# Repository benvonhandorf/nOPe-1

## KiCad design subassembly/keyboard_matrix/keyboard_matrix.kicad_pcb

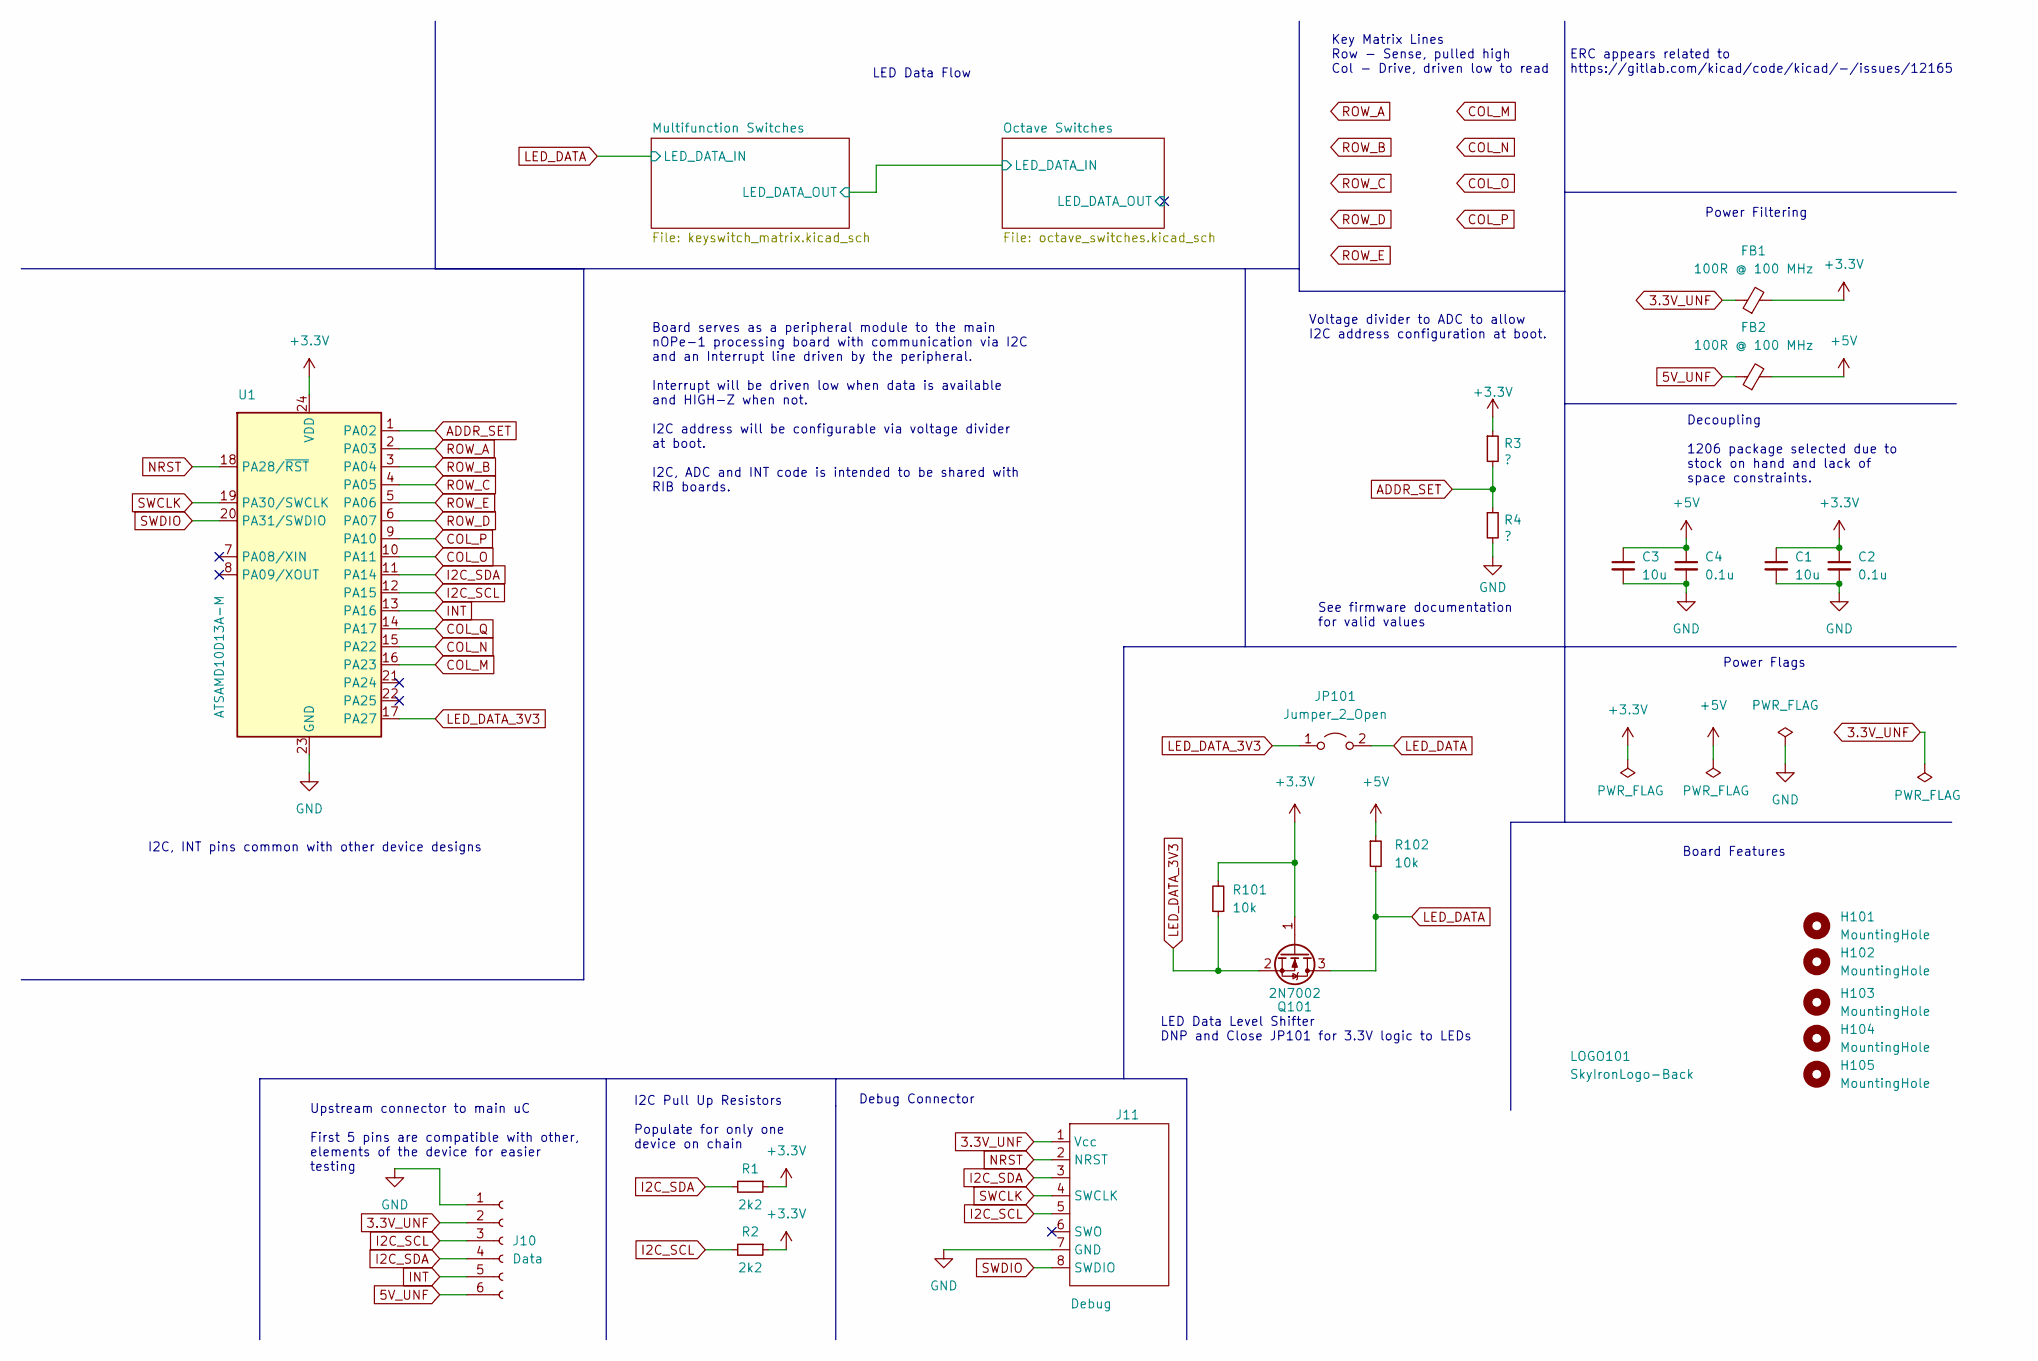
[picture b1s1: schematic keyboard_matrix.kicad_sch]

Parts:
C1, C3: 10u; C_1206_3216Metric_Pad1.33x1.80mm_HandSolder
C2, C4: 0.1u; C_1206_3216Metric_Pad1.33x1.80mm_HandSolder
FB1, FB2: 100R @ 100 MHz; R_0805_2012Metric_Pad1.20x1.40mm_HandSolder
H101, H102, H103, H104, H105: MountingHole; MountingHole_3.2mm_M3_DIN965
J10: Data; PinHeader_1x06_P2.54mm_Vertical
J11: Debug; SOICbite_renumbered
JP101: Jumper_2_Open; SolderJumper-2_P1.3mm_Open_Pad1.0x1.5mm
LOGO101: SkyIronLogo-Back; SkyIron_logo_Back
Q101: 2N7002; SOT-23
R1, R2: 2k2; R_0603_1608Metric
R3, R4: ?; R_0603_1608Metric
R101, R102: 10k; R_0805_2012Metric_Pad1.20x1.40mm_HandSolder
U1: ATSAMD10D13A-M; QFN-24-1EP_4x4mm_P0.5mm_EP2.6x2.6mm

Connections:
3.3V_UNF: FB1.1, J10.2, J11.1 (Vcc)
5V_UNF: FB2.1, J10.6
+3.3V: C1.1, C2.1, FB1.2, Q101.1 (G), R1.1, R2.1, R3.1, R101.2, U1.24 (VDD)
+5V: C3.1, C4.1, FB2.2, R102.1; also elsewhere on the board
ADDR_SET: R3.2, R4.1, U1.1 (PA02)
COL_M: U1.16 (PA23); also elsewhere on the board
COL_N: U1.15 (PA22); also elsewhere on the board
COL_O: U1.10 (PA11); also elsewhere on the board
COL_P: U1.9 (PA10); also elsewhere on the board
COL_Q: U1.14 (PA17); also elsewhere on the board
GND: C1.2, C2.2, C3.2, C4.2, J10.1, J11.7 (GND), R4.2, U1.23 (GND), U1.25 (GND); also elsewhere on the board
I2C_SCL: J10.3, J11.5, R2.2, U1.12 (PA15)
I2C_SDA: J10.4, J11.3, R1.2, U1.11 (PA14)
INT: J10.5, U1.13 (PA16)
LED_DATA: JP101.2 (B), Q101.3 (D), R102.2; also elsewhere on the board
LED_DATA_3V3: JP101.1 (A), Q101.2 (S), R101.1, U1.17 (PA27)
NRST: J11.2 (NRST), U1.18 (PA28/~RST)
ROW_A: U1.2 (PA03); also elsewhere on the board
ROW_B: U1.3 (PA04); also elsewhere on the board
ROW_C: U1.4 (PA05); also elsewhere on the board
ROW_D: U1.6 (PA07); also elsewhere on the board
ROW_E: U1.5 (PA06); also elsewhere on the board
SWCLK: J11.4 (SWCLK), U1.19 (PA30/SWCLK)
SWDIO: J11.8 (SWDIO), U1.20 (PA31/SWDIO)

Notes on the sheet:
I2C, INT pins common with other device designs
LED Data Flow
Upstream connector to main uC First 5 pins are compatible with other, elements of the device for easier testing
Power Flags
Voltage divider to ADC to allow I2C address configuration at boot.
LED Data Level Shifter DNP and Close JP101 for 3.3V logic to LEDs
I2C Pull Up Resistors Populate for only one device on chain
Board Features
Key Matrix Lines Row - Sense, pulled high Col - Drive, driven low to read
See firmware documentation for valid values
Debug Connector
Board serves as a peripheral module to the main nOPe-1 processing board with communication via I2C and an Interrupt line driven by the peripheral. Interrupt will be driven low when data is available and HIGH-Z when not. I2C address will be configurable via voltage divider at boot. I2C, ADC and INT 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
ERC appears related to https://gitlab.com/kicad/code/kicad/-/issues/12165
Decoupling 1206 package selected due to stock on hand and lack of space constraints.
Power Filtering

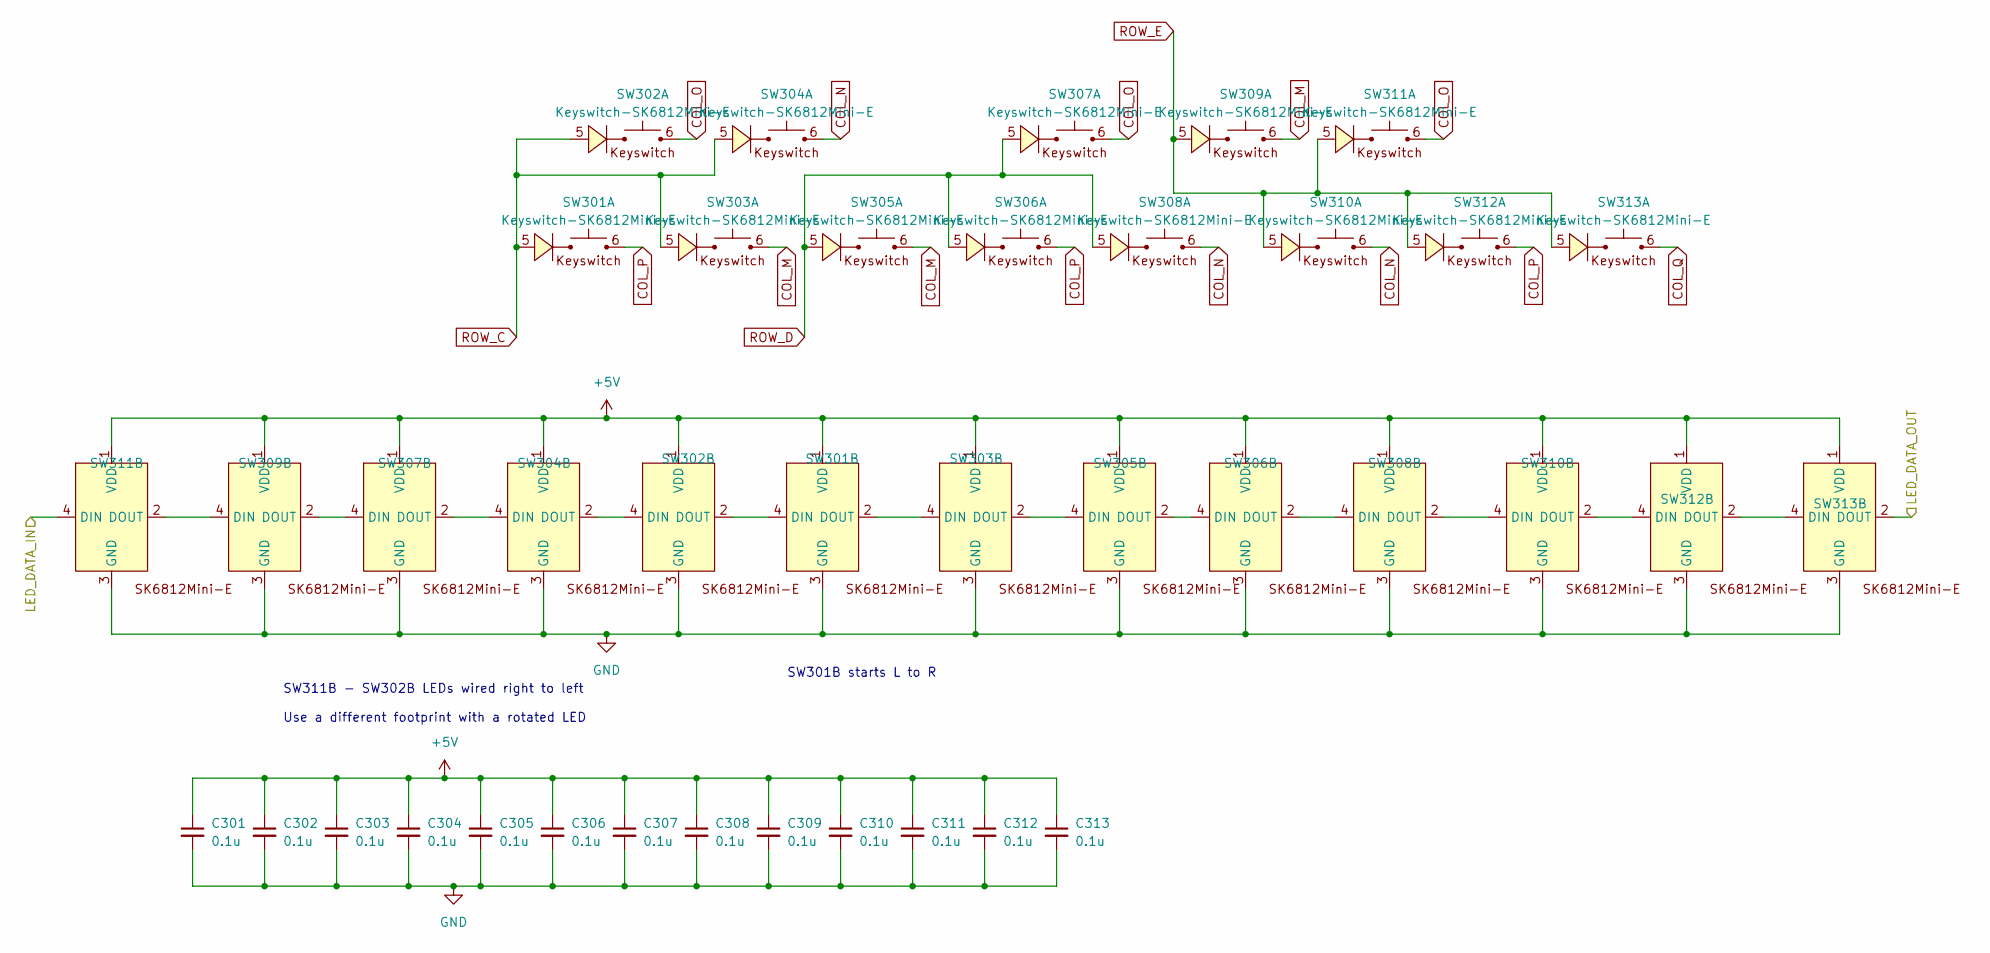
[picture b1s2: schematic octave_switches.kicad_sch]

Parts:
C301, C302, C303, C304, C305, C306, C307, C308, C309, C310, C311, C312, C313: 0.1u; C_1206_3216Metric_Pad1.33x1.80mm_HandSolder
SW301, SW303, SW305, SW306: Keyswitch-SK6812Mini-E; Keyswitch_Choc_SK6812_Diode_Vert_L
SW302, SW304, SW307, SW309, SW311: Keyswitch-SK6812Mini-E; Keyswitch_Choc_w_SK6812Mini-E_Back_SOD-103_Diode_RtoL
SW308, SW310, SW312, SW313: Keyswitch-SK6812Mini-E; Keyswitch_Choc_SK6812_Diode_Vert_R

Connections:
+5V: C301.1, C302.1, C303.1, C304.1, C305.1, C306.1, C307.1, C308.1, C309.1, C310.1, C311.1, C312.1, C313.1, SW301.1 (VDD), SW302.1 (VDD), SW303.1 (VDD), SW304.1 (VDD), SW305.1 (VDD), SW306.1 (VDD), SW307.1 (VDD), SW308.1 (VDD), SW309.1 (VDD), SW310.1 (VDD), SW311.1 (VDD), SW312.1 (VDD), SW313.1 (VDD); also elsewhere on the board
/Multifunction Switches/LED_DATA_OUT: SW311.4 (DIN); also elsewhere on the board
/Octave Switches/LED_DATA_OUT: SW313.2 (DOUT)
COL_M: SW303.6, SW305.6, SW309.6; also elsewhere on the board
COL_N: SW304.6, SW308.6, SW310.6; also elsewhere on the board
COL_O: SW302.6, SW307.6, SW311.6; also elsewhere on the board
COL_P: SW301.6, SW306.6, SW312.6; also elsewhere on the board
COL_Q: SW313.6; also elsewhere on the board
GND: C301.2, C302.2, C303.2, C304.2, C305.2, C306.2, C307.2, C308.2, C309.2, C310.2, C311.2, C312.2, C313.2, SW301.3 (GND), SW302.3 (GND), SW303.3 (GND), SW304.3 (GND), SW305.3 (GND), SW306.3 (GND), SW307.3 (GND), SW308.3 (GND), SW309.3 (GND), SW310.3 (GND), SW311.3 (GND), SW312.3 (GND), SW313.3 (GND); also elsewhere on the board
unnamed: SW301.2 (DOUT), SW303.4 (DIN)
unnamed: SW301.4 (DIN), SW302.2 (DOUT)
unnamed: SW302.4 (DIN), SW304.2 (DOUT)
unnamed: SW303.2 (DOUT), SW305.4 (DIN)
unnamed: SW304.4 (DIN), SW307.2 (DOUT)
unnamed: SW305.2 (DOUT), SW306.4 (DIN)
unnamed: SW306.2 (DOUT), SW308.4 (DIN)
unnamed: SW307.4 (DIN), SW309.2 (DOUT)
unnamed: SW308.2 (DOUT), SW310.4 (DIN)
unnamed: SW309.4 (DIN), SW311.2 (DOUT)
unnamed: SW310.2 (DOUT), SW312.4 (DIN)
unnamed: SW312.2 (DOUT), SW313.4 (DIN)
ROW_C: SW301.5, SW302.5, SW303.5, SW304.5; also elsewhere on the board
ROW_D: SW305.5, SW306.5, SW307.5, SW308.5; also elsewhere on the board
ROW_E: SW309.5, SW310.5, SW311.5, SW312.5, SW313.5; also elsewhere on the board

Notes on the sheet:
SW301B starts L to R
SW311B - SW302B LEDs wired right to left Use a different footprint with a rotated LED

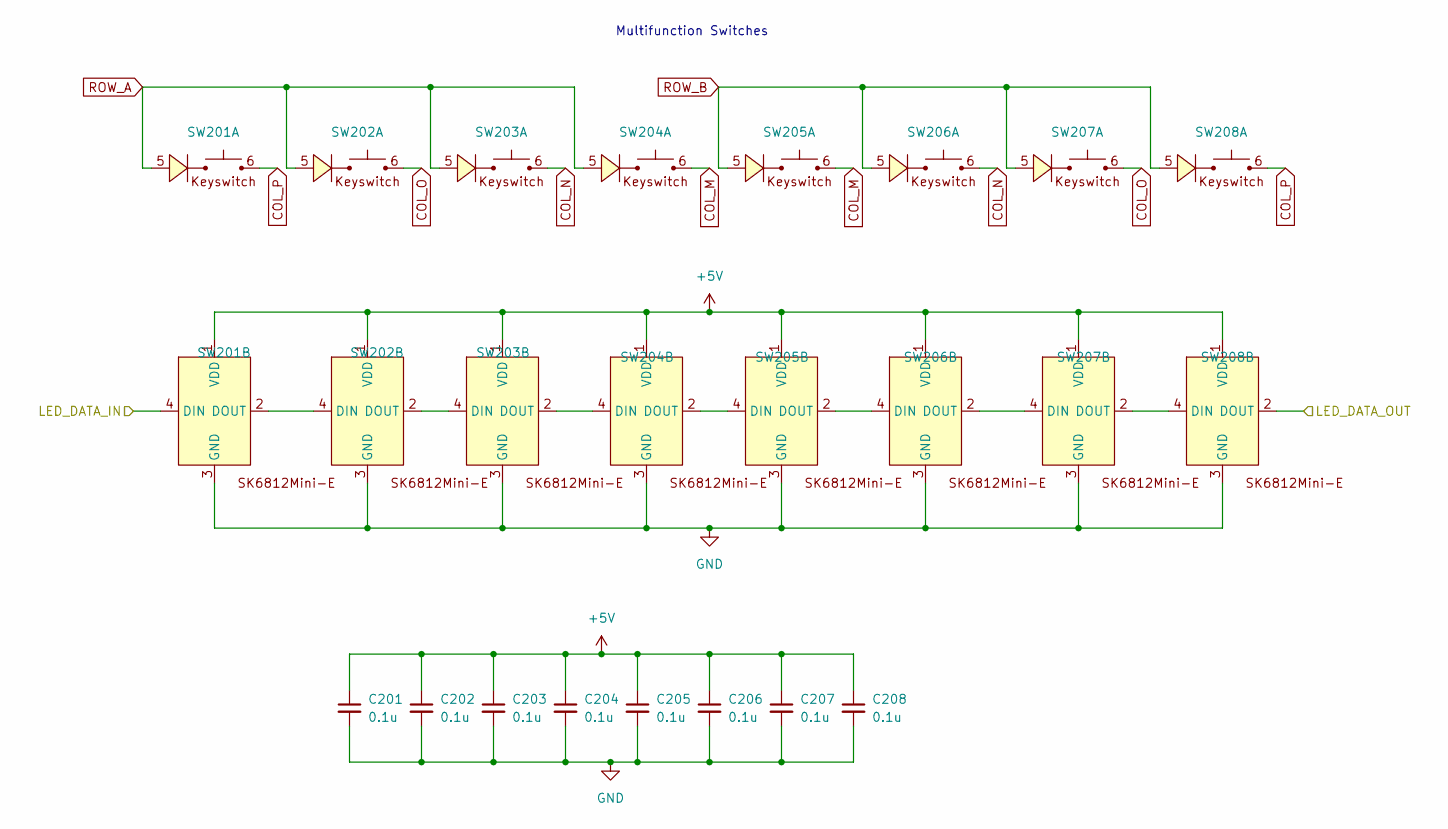
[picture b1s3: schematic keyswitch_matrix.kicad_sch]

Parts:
C201, C202, C203, C204, C205, C206, C207, C208: 0.1u; C_1206_3216Metric_Pad1.33x1.80mm_HandSolder
SW201, SW202, SW203, SW204, SW205, SW206, SW207, SW208: Keyswitch-SK6812Mini-E; Keyswitch_Choc_w_SK6812Mini-E_Back_SOD-103_Diode_LtoR

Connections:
+5V: C201.1, C202.1, C203.1, C204.1, C205.1, C206.1, C207.1, C208.1, SW201.1 (VDD), SW202.1 (VDD), SW203.1 (VDD), SW204.1 (VDD), SW205.1 (VDD), SW206.1 (VDD), SW207.1 (VDD), SW208.1 (VDD); also elsewhere on the board
/Multifunction Switches/LED_DATA_OUT: SW208.2 (DOUT); also elsewhere on the board
COL_M: SW204.6, SW205.6; also elsewhere on the board
COL_N: SW203.6, SW206.6; also elsewhere on the board
COL_O: SW202.6, SW207.6; also elsewhere on the board
COL_P: SW201.6, SW208.6; also elsewhere on the board
GND: C201.2, C202.2, C203.2, C204.2, C205.2, C206.2, C207.2, C208.2, SW201.3 (GND), SW202.3 (GND), SW203.3 (GND), SW204.3 (GND), SW205.3 (GND), SW206.3 (GND), SW207.3 (GND), SW208.3 (GND); also elsewhere on the board
LED_DATA: SW201.4 (DIN); also elsewhere on the board
unnamed: SW201.2 (DOUT), SW202.4 (DIN)
unnamed: SW202.2 (DOUT), SW203.4 (DIN)
unnamed: SW203.2 (DOUT), SW204.4 (DIN)
unnamed: SW204.2 (DOUT), SW205.4 (DIN)
unnamed: SW205.2 (DOUT), SW206.4 (DIN)
unnamed: SW206.2 (DOUT), SW207.4 (DIN)
unnamed: SW207.2 (DOUT), SW208.4 (DIN)
ROW_A: SW201.5, SW202.5, SW203.5, SW204.5; also elsewhere on the board
ROW_B: SW205.5, SW206.5, SW207.5, SW208.5; also elsewhere on the board

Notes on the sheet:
Multifunction Switches

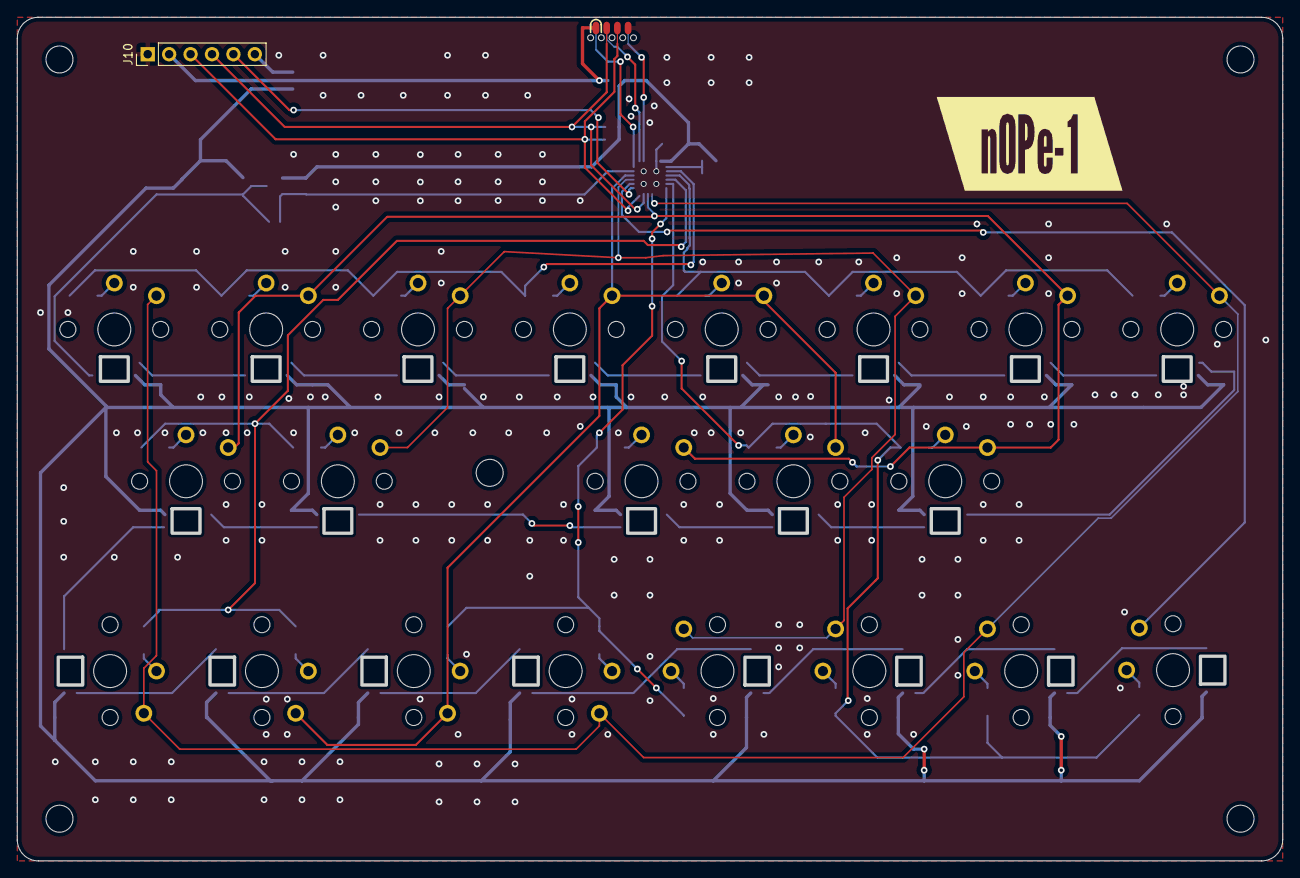
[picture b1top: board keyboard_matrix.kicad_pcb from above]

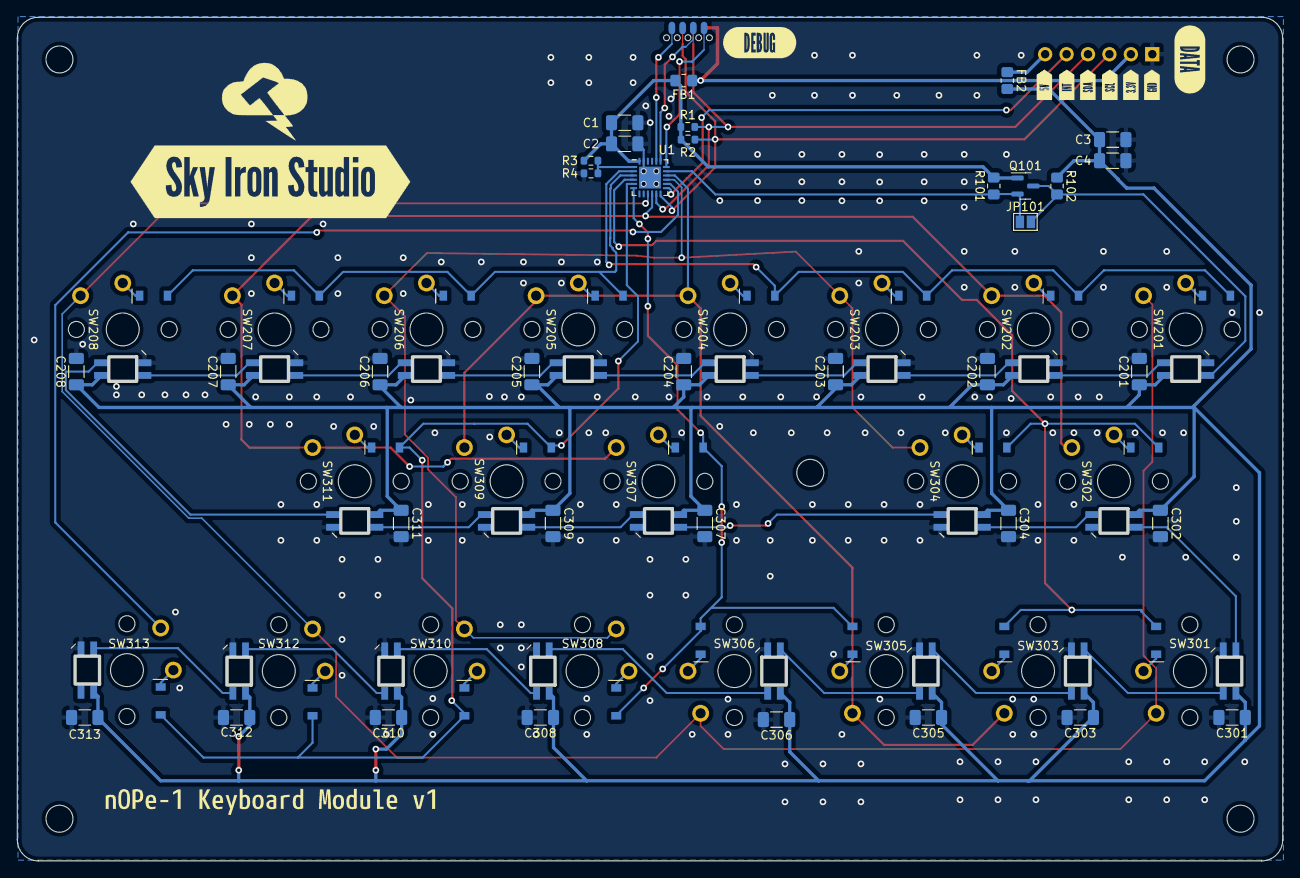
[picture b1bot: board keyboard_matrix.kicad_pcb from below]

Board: 2 copper layers, 149.7 x 99.7 mm, 76 parts (46 on the bottom side), 44 nets.

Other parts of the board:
kibuzzard-6388C4FD: G***; kibuzzard-6388C4FD
kibuzzard-6388C06F: G***; kibuzzard-6388C06F
kibuzzard-6388C51A: G***; kibuzzard-6388C51A
kibuzzard-6388C61B: G***; kibuzzard-6388C61B
kibuzzard-6388C408: G***; kibuzzard-6388C408
kibuzzard-6388C475: G***; kibuzzard-6388C475
kibuzzard-6388C535: G***; kibuzzard-6388C535
kibuzzard-6388C552: G***; kibuzzard-6388C552
kibuzzard-6388C567: G***; kibuzzard-6388C567
kibuzzard-6388C579: G***; kibuzzard-6388C579
kibuzzard-6388D403: G***; kibuzzard-6388D403

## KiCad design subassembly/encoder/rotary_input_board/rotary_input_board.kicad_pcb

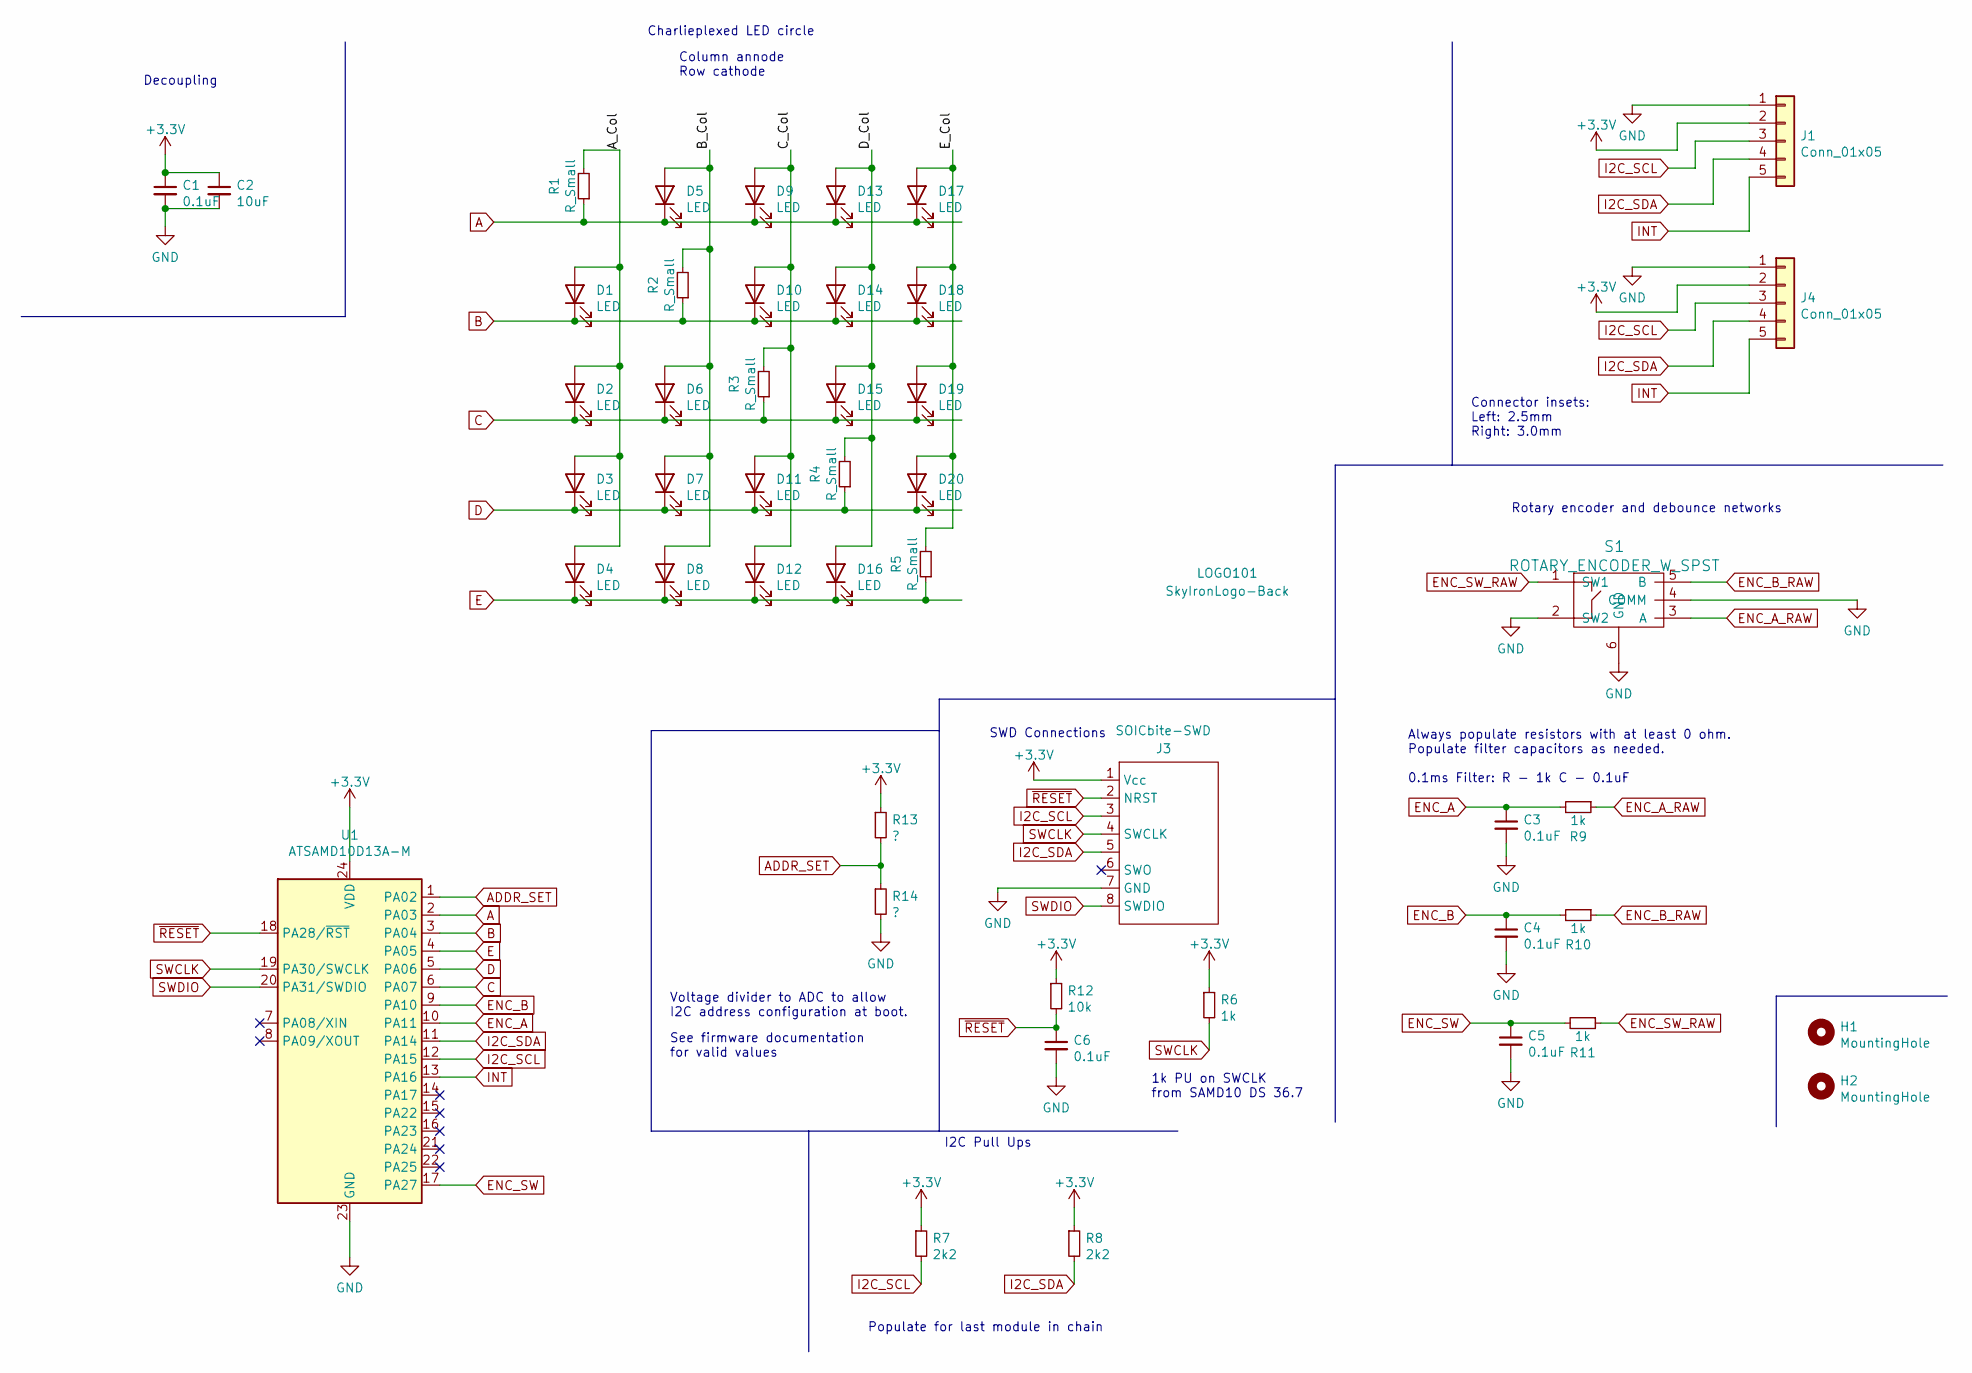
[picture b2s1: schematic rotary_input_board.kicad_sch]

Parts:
C1, C3, C4, C5, C6: 0.1uF; C_0603_1608Metric
C2: 10uF; C_0805_2012Metric
D1, D2, D3, D4, D5, D6, D7, D8, D9, D10, D11, D12, D13, D14, D15, D16, D17, D18, D19, D20: LED; LED_0603_1608Metric
H1, H2: MountingHole; MountingHole_2.5mm
J1, J4: Conn_01x05; PinSocket_1x05_P1.27mm_Vertical
J3: SOICbite-SWD; SOICbite_renumbered
LOGO101: SkyIronLogo-Back; SkyIron_logo_Back
R1, R2, R3, R4, R5: R_Small; R_0603_1608Metric
R6, R9, R10, R11: 1k; R_0603_1608Metric
R7, R8: 2k2; R_0603_1608Metric
R12: 10k; R_0603_1608Metric
R13, R14: ?; R_0603_1608Metric
S1: ROTARY_ENCODER_W_SPST; Rotary_Encoder_W_Switch
U1: ATSAMD10D13A-M; QFN-24-1EP_4x4mm_P0.5mm_EP2.6x2.6mm

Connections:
+3.3V: C1.1, C2.1, J1.2, J3.1 (Vcc), J4.2, R6.1, R7.1, R8.1, R12.1, R13.1, U1.24 (VDD)
/A_Col: D1.2 (A), D2.2 (A), D3.2 (A), D4.2 (A), R1.2
/B_Col: D5.2 (A), D6.2 (A), D7.2 (A), D8.2 (A), R2.2
/C_Col: D9.2 (A), D10.2 (A), D11.2 (A), D12.2 (A), R3.2
/D_Col: D13.2 (A), D14.2 (A), D15.2 (A), D16.2 (A), R4.2
/E_Col: D17.2 (A), D18.2 (A), D19.2 (A), D20.2 (A), R5.2
A: D5.1 (K), D9.1 (K), D13.1 (K), D17.1 (K), R1.1, U1.2 (PA03)
ADDR_SET: R13.2, R14.1, U1.1 (PA02)
B: D1.1 (K), D10.1 (K), D14.1 (K), D18.1 (K), R2.1, U1.3 (PA04)
C: D2.1 (K), D6.1 (K), D15.1 (K), D19.1 (K), R3.1, U1.6 (PA07)
D: D3.1 (K), D7.1 (K), D11.1 (K), D20.1 (K), R4.1, U1.5 (PA06)
E: D4.1 (K), D8.1 (K), D12.1 (K), D16.1 (K), R5.1, U1.4 (PA05)
ENC_A: C3.1, R9.2, U1.10 (PA11)
ENC_A_RAW: R9.1, S1.3 (A)
ENC_B: C4.1, R10.2, U1.9 (PA10)
ENC_B_RAW: R10.1, S1.5 (B)
ENC_SW: C5.1, R11.2, U1.17 (PA27)
ENC_SW_RAW: R11.1, S1.1 (SW1)
GND: C1.2, C2.2, C3.2, C4.2, C5.2, C6.2, J1.1, J3.7 (GND), J4.1, R14.2, S1.2 (SW2), S1.4 (COMM), S1.6 (GND), U1.23 (GND), U1.25 (GND)
I2C_SCL: J1.3, J3.3, J4.3, R7.2, U1.12 (PA15)
I2C_SDA: J1.4, J3.5, J4.4, R8.2, U1.11 (PA14)
INT: J1.5, J4.5, U1.13 (PA16)
SWCLK: J3.4 (SWCLK), R6.2, U1.19 (PA30/SWCLK)
SWDIO: J3.8 (SWDIO), U1.20 (PA31/SWDIO)
~RESET: C6.1, J3.2 (NRST), R12.2, U1.18 (PA28/~RST)

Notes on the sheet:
1k PU on SWCLK from SAMD10 DS 36.7
Populate for last module in chain
Rotary encoder and debounce networks
I2C Pull Ups
See firmware documentation for valid values
Column annode Row cathode
Voltage divider to ADC to allow I2C address configuration at boot.
SWD Connections
Decoupling
Charlieplexed LED circle
Connector insets: Left: 2.5mm Right: 3.0mm
Always populate resistors with at least 0 ohm. Populate filter capacitors as needed. 0.1ms Filter: R - 1k C - 0.1uF

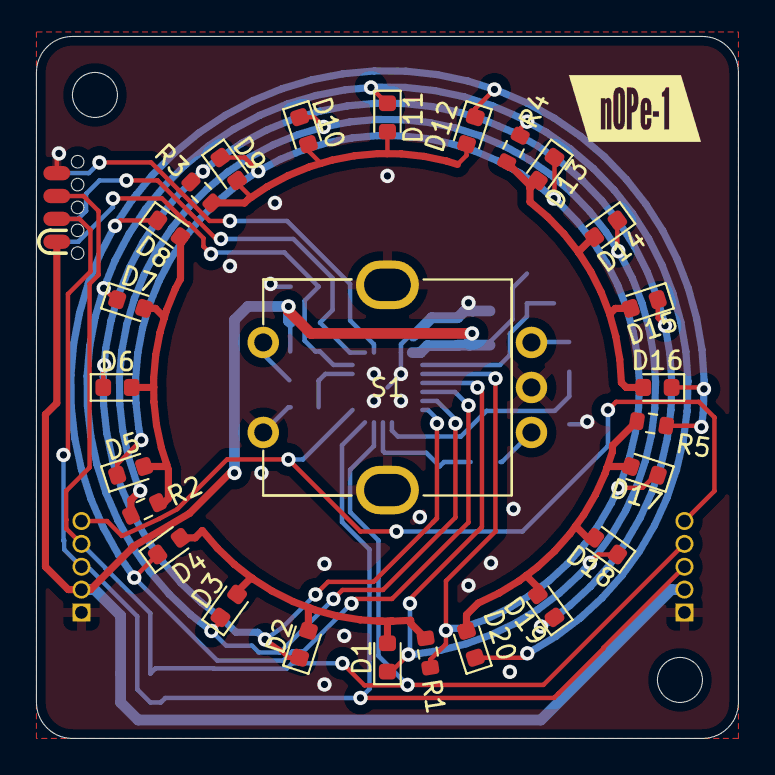
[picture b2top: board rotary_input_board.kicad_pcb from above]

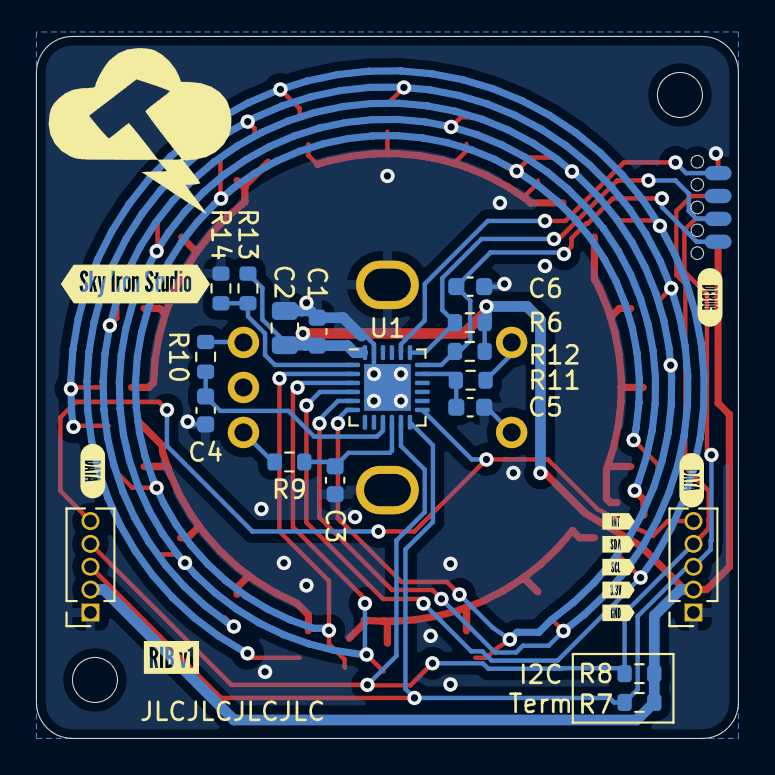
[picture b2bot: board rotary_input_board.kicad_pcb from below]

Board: 4 copper layers, 39.0 x 39.0 mm, 59 parts (28 on the bottom side), 25 nets.

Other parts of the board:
kibuzzard-63921B01: G***; kibuzzard-63921B01
kibuzzard-63921BF7: G***; kibuzzard-63921BF7
kibuzzard-63921CC8: G***; kibuzzard-63921CC8
kibuzzard-63921CE0: G***; kibuzzard-63921CE0
kibuzzard-63921CF0: G***; kibuzzard-63921CF0
kibuzzard-63921CFB: G***; kibuzzard-63921CFB
kibuzzard-63921D08: G***; kibuzzard-63921D08
kibuzzard-63921DF1, kibuzzard-63921DF1#2: G***; kibuzzard-63921DF1
kibuzzard-63921E31: G***; kibuzzard-63921E31
kibuzzard-639219D7: G***; kibuzzard-639219D7

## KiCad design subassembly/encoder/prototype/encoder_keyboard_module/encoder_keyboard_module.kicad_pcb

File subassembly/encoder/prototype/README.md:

## Prototype Pinouts

- J1 - Communication header
  - 1 GND
  - 2 3.3V
  - 3 i2c SCL
  - 4 i2c SDA
  - 5 INT
- J2 - Programming Header
  - 1 GND
  - 2 3.3V
  - 3 ~RESET
  - 4 SWCLK
  - 5 SWDIO

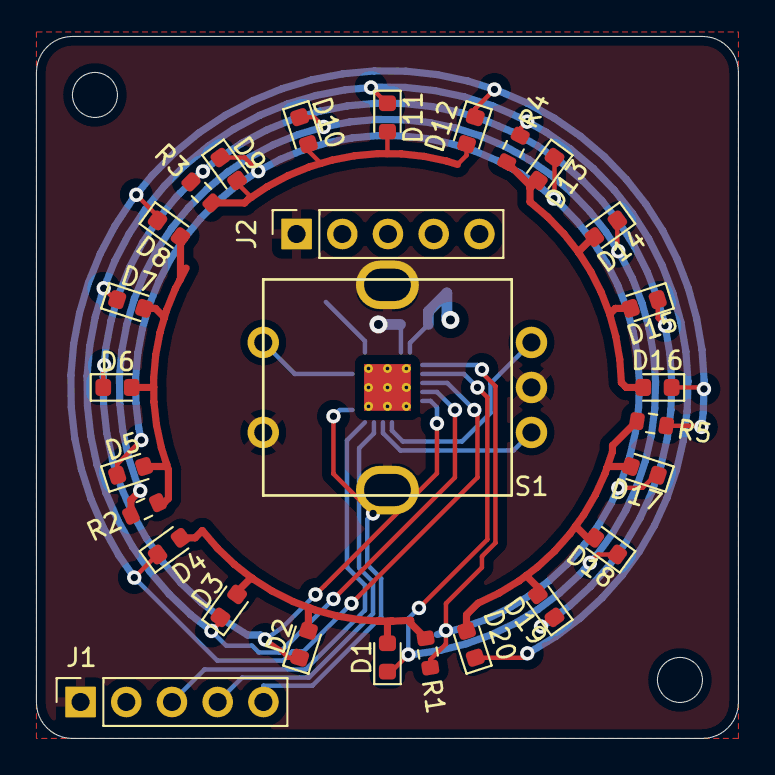
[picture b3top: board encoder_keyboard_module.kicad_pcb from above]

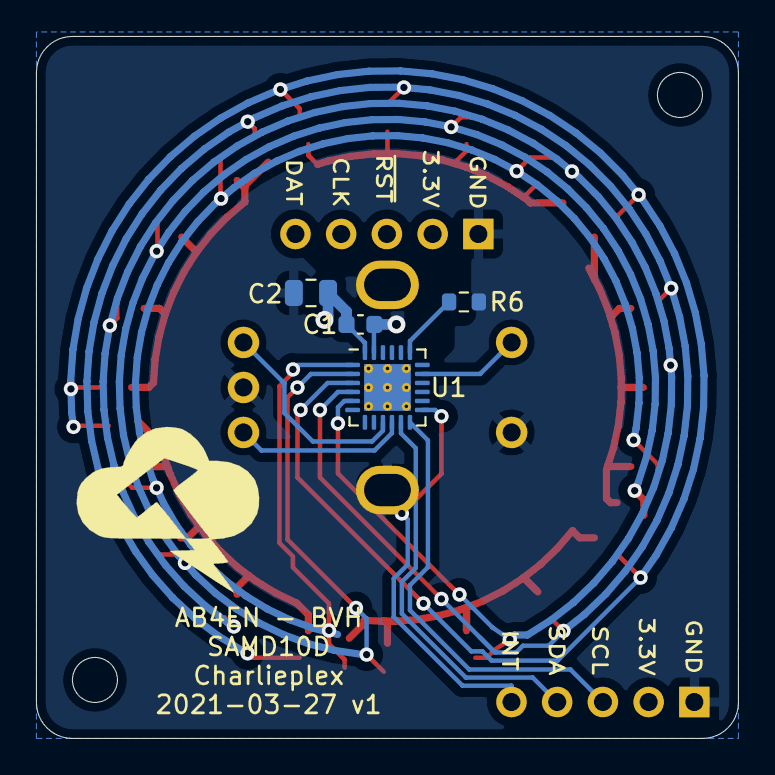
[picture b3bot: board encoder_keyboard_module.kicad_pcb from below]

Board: 4 copper layers, 39.0 x 39.0 mm, 34 parts (4 on the bottom side), 21 nets.

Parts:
C1: 0.1uF; C_0603_1608Metric
C2: 10uF; C_0805_2012Metric
D1, D2, D3, D4, D5, D6, D7, D8, D9, D10, D11, D12, D13, D14, D15, D16, D17, D18, D19, D20: LED; LED_0603_1608Metric
H1, H2: MountingHole; MountingHole_2.5mm
J1, J2: Conn_01x05; PinSocket_1x05_P2.54mm_Vertical
R1, R2, R3, R4, R5: R_Small; R_0603_1608Metric
R6: 1k; R_0603_1608Metric
S1: ROTARY_ENCODER_W_SPST; Rotary_Encoder_W_Switch
U1: ATSAMD10D13A-M; QFN-24-1EP_4x4mm_P0.5mm_EP2.6x2.6mm_ThermalVias

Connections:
+3V3: C1.1, C2.1, J1.2, J2.2, R6.1, U1.24 (VDD)
/A_Col: D1.2 (A), D2.2 (A), D3.2 (A), D4.2 (A), R1.2
/B_Col: D5.2 (A), D6.2 (A), D7.2 (A), D8.2 (A), R2.2
/C_Col: D9.2 (A), D10.2 (A), D11.2 (A), D12.2 (A), R3.2
/D_Col: D13.2 (A), D14.2 (A), D15.2 (A), D16.2 (A), R4.2
/E_Col: D17.2 (A), D18.2 (A), D19.2 (A), D20.2 (A), R5.2
A: D5.1 (K), D9.1 (K), D13.1 (K), D17.1 (K), R1.1, U1.1 (PA02)
B: D1.1 (K), D10.1 (K), D14.1 (K), D18.1 (K), R2.1, U1.2 (PA03)
C: D2.1 (K), D6.1 (K), D15.1 (K), D19.1 (K), R3.1, U1.5 (PA06)
D: D3.1 (K), D7.1 (K), D11.1 (K), D20.1 (K), R4.1, U1.4 (PA05)
E: D4.1 (K), D8.1 (K), D12.1 (K), D16.1 (K), R5.1, U1.3 (PA04)
ENC_A: S1.3 (A), U1.10 (PA11)
ENC_B: S1.5 (B), U1.9 (PA10)
ENC_SW: S1.1 (SW1), U1.17 (PA27)
GND: C1.2, C2.2, J1.1, J2.1, S1.2 (SW2), S1.4 (COMM), S1.6 (GND), U1.23 (GND)
I2C_SCL: J1.3, U1.12 (PA15)
I2C_SDA: J1.4, U1.11 (PA14)
INT: J1.5, U1.13 (PA16)
SWCLK: J2.4, R6.2, U1.19 (PA30/SWCLK)
SWDIO: J2.5, U1.20 (PA31/SWDIO)
~RESET: J2.3, U1.18 (PA28/~RST)

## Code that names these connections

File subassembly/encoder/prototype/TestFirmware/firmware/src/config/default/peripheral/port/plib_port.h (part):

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#define LED_C_Get()               (((PORT_REGS->GROUP[0].PORT_IN >> 6U)) & 0x01U)
#define LED_C_PIN                  PORT_PIN_PA06

/*** Macros for ENC_B pin ***/
#define ENC_B_Set()               (PORT_REGS->GROUP[0].PORT_OUTSET = ((uint32_t)1U << 10U))
#define ENC_B_Clear()             (PORT_REGS->GROUP[0].PORT_OUTCLR = ((uint32_t)1U << 10U))
#define ENC_B_Toggle()            (PORT_REGS->GROUP[0].PORT_OUTTGL = ((uint32_t)1U << 10U))
#define ENC_B_OutputEnable()      (PORT_REGS->GROUP[0].PORT_DIRSET = ((uint32_t)1U << 10U))
#define ENC_B_InputEnable()       (PORT_REGS->GROUP[0].PORT_DIRCLR = ((uint32_t)1U << 10U))
#define ENC_B_Get()               (((PORT_REGS->GROUP[0].PORT_IN >> 10U)) & 0x01U)
#define ENC_B_PIN                  PORT_PIN_PA10

/*** Macros for ENC_A pin ***/
#define ENC_A_Get()               (((PORT_REGS->GROUP[0].PORT_IN >> 11U)) & 0x01U)
#define ENC_A_PIN                  PORT_PIN_PA11

/*** Macros for INT_OUT pin ***/
#define INT_OUT_Set()               (PORT_REGS->GROUP[0].PORT_OUTSET = ((uint32_t)1U << 16U))
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#define INT_OUT_Get()               (((PORT_REGS->GROUP[0].PORT_IN >> 16U)) & 0x01U)
#define INT_OUT_PIN                  PORT_PIN_PA16

/*** Macros for ENC_SW pin ***/
#define ENC_SW_Get()               (((PORT_REGS->GROUP[0].PORT_IN >> 27U)) & 0x01U)
#define ENC_SW_PIN                  PORT_PIN_PA27

/*** Macros for RESET_N pin ***/
#define RESET_N_Get()               (((PORT_REGS->GROUP[0].PORT_IN >> 28U)) & 0x01U)
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
typedef enum
{
    /* PA02 pin */
    PORT_PIN_PA02 = 2U,

    /* PA03 pin */
    PORT_PIN_PA03 = 3U,

    /* PA04 pin */
    PORT_PIN_PA04 = 4U,

    /* PA05 pin */
    PORT_PIN_PA05 = 5U,

    /* PA06 pin */
    PORT_PIN_PA06 = 6U,

    /* PA07 pin */
    PORT_PIN_PA07 = 7U,

    /* PA08 pin */
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    /* PA09 pin */
    PORT_PIN_PA09 = 9U,

    /* PA10 pin */
    PORT_PIN_PA10 = 10U,

    /* PA11 pin */
    PORT_PIN_PA11 = 11U,

    /* PA14 pin */
    PORT_PIN_PA14 = 14U,

    /* PA15 pin */
    PORT_PIN_PA15 = 15U,

    /* PA16 pin */
    PORT_PIN_PA16 = 16U,

    /* PA17 pin */
    PORT_PIN_PA17 = 17U,

    /* PA22 pin */
    PORT_PIN_PA22 = 22U,

    /* PA23 pin */
    PORT_PIN_PA23 = 23U,

    /* PA24 pin */
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    /* PA25 pin */
    PORT_PIN_PA25 = 25U,

    /* PA27 pin */
    PORT_PIN_PA27 = 27U,

    /* PA28 pin */
    PORT_PIN_PA28 = 28U,

    /* PA30 pin */
    PORT_PIN_PA30 = 30U,

    /* PA31 pin */
    PORT_PIN_PA31 = 31U,

    /* This element should not be used in any of the PORT APIs.
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
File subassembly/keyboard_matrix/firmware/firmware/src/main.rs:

#![no_std]
#![no_main]

mod i2c_peripheral;
mod kib_board;
mod protocol;

use core::borrow::Borrow;

#[cfg(not(feature = "use_semihosting"))]
use panic_halt as _;
#[cfg(feature = "use_semihosting")]
use panic_semihosting as _;

use kib_board as bsp;

use bsp::entry;
use bsp::hal;
use bsp::pac;

use cortex_m::interrupt as interrupt_helpers;
use cortex_m::peripheral::NVIC;
use pac::interrupt;
use pac::{CorePeripherals, Peripherals};

use hal::clock::GenericClockController;
use hal::delay::Delay;
use hal::prelude::*;
use hal::sercom::i2c;
use hal::sercom::Sercom;
use hal::time::*;
use hal::timer::*;

use ws2812_timer_delay as ws2812;

use keyboard_matrix::KeyboardMatrix;
use synth_engine::SynthEngine;

use illuminator::IlluminationEngine;

#[entry]
fn main() -> ! {
    //Initial hardware configuration
    let mut peripherals = Peripherals::take().unwrap();
    let mut core = CorePeripherals::take().unwrap();
    let mut clocks = GenericClockController::with_internal_32kosc(
        peripherals.GCLK,
        &mut peripherals.PM,
        &mut peripherals.SYSCTRL,
        &mut peripherals.NVMCTRL,
    );

    let gclk0 = clocks.gclk0();
    let tc12 = &clocks.tc1_tc2(&gclk0).unwrap();

    let pins = bsp::Pins::new(peripherals.PORT);

    //Configure I2C
    let sercom0_clock = &clocks.sercom0_core(&gclk0).unwrap();
    let pads = i2c::Pads::new(pins.sda, pins.scl);

    let mut sercom0 = peripherals.SERCOM0;

    sercom0.enable_apb_clock(&peripherals.PM);

    let output_pin = Some(pins.int.into_push_pull_output());

    i2c_peripheral::configure_bus_status(output_pin);

    i2c_peripheral::configure_sercom0(sercom0, 0x22);

    unsafe {
        core.NVIC.set_priority(interrupt::SERCOM0, 1);
        NVIC::unmask(interrupt::SERCOM0);
    }

    let mut delay = Delay::new(core.SYST, &mut clocks);

    let mut synth_engine = SynthEngine::new();

    let mut keyboard_matrix = KeyboardMatrix::new(
        pins.row_a.into_push_pull_output(),
        pins.row_b.into_push_pull_output(),
        pins.row_c.into_push_pull_output(),
        pins.row_d.into_push_pull_output(),
        pins.row_e.into_push_pull_output(),
        pins.col_n.into_pull_down_input(),
        pins.col_m.into_pull_down_input(),
        pins.col_o.into_pull_down_input(),
        pins.col_p.into_pull_down_input(),
        pins.col_q.into_pull_down_input(),
    );

    let mut led_timer = TimerCounter::tc1_(tc12, peripherals.TC1, &mut peripherals.PM);
    led_timer.start(MegaHertz::MHz(7).into_duration());

    let mut led_data_pin = pins.led_data.into_push_pull_output();
    led_data_pin.set_drive_strength(true);

    let mut led_strand = ws2812::Ws2812::new(led_timer, led_data_pin);

    let mut illumination_engine = IlluminationEngine::new(&mut led_strand);

    let delta_t_ms = 2;

    let mut communication_register: u8 = 0x00;

    loop {
        //Process protocol commands
        let command = interrupt_helpers::free(|cs| {
            if let Some(comms_status) = i2c_peripheral::BUS_STATUS.borrow(cs).borrow_mut().as_mut()
            {
                comms_status.process()
            } else {
                None
            }
        });

        if let Some(command) = command {
            communication_register = command.register;

            protocol::process_command(&command, &mut synth_engine, &mut illumination_engine);
        }

        let keystate = keyboard_matrix.scan(&mut delay);

        // Update Synth Engine state
        synth_engine.update(&keystate);

        illumination_engine.update(delta_t_ms, &keystate, &synth_engine.state);

        illumination_engine.render();

        //Update protocol response
        //Note that this should be imdepotent.  If not, should check `can_provide_data` first.
        if let Some((register_data, data_size)) =
            protocol::build_response(communication_register, &synth_engine, &illumination_engine)
        {
            interrupt_helpers::free(|cs| {
                if let Some(comms_status) =
                    i2c_peripheral::BUS_STATUS.borrow(cs).borrow_mut().as_mut()
                {
                    if comms_status.can_provide_data() {
                        comms_status.provide_data(communication_register, &register_data, data_size);
                    }
                }
            });
        }
    }
}

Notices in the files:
subassembly/encoder/prototype/TestFirmware/firmware/src/config/default/peripheral/port/plib_port.h:
Copyright (C) 2018 Microchip Technology Inc. and its subsidiaries.
